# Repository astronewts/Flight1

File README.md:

Flight1
=======

Arduino Code for the 'Around the World' Flight

The flight control software uses a number of custom libraries, to install on a Mac please run:

./installLibraries.sh

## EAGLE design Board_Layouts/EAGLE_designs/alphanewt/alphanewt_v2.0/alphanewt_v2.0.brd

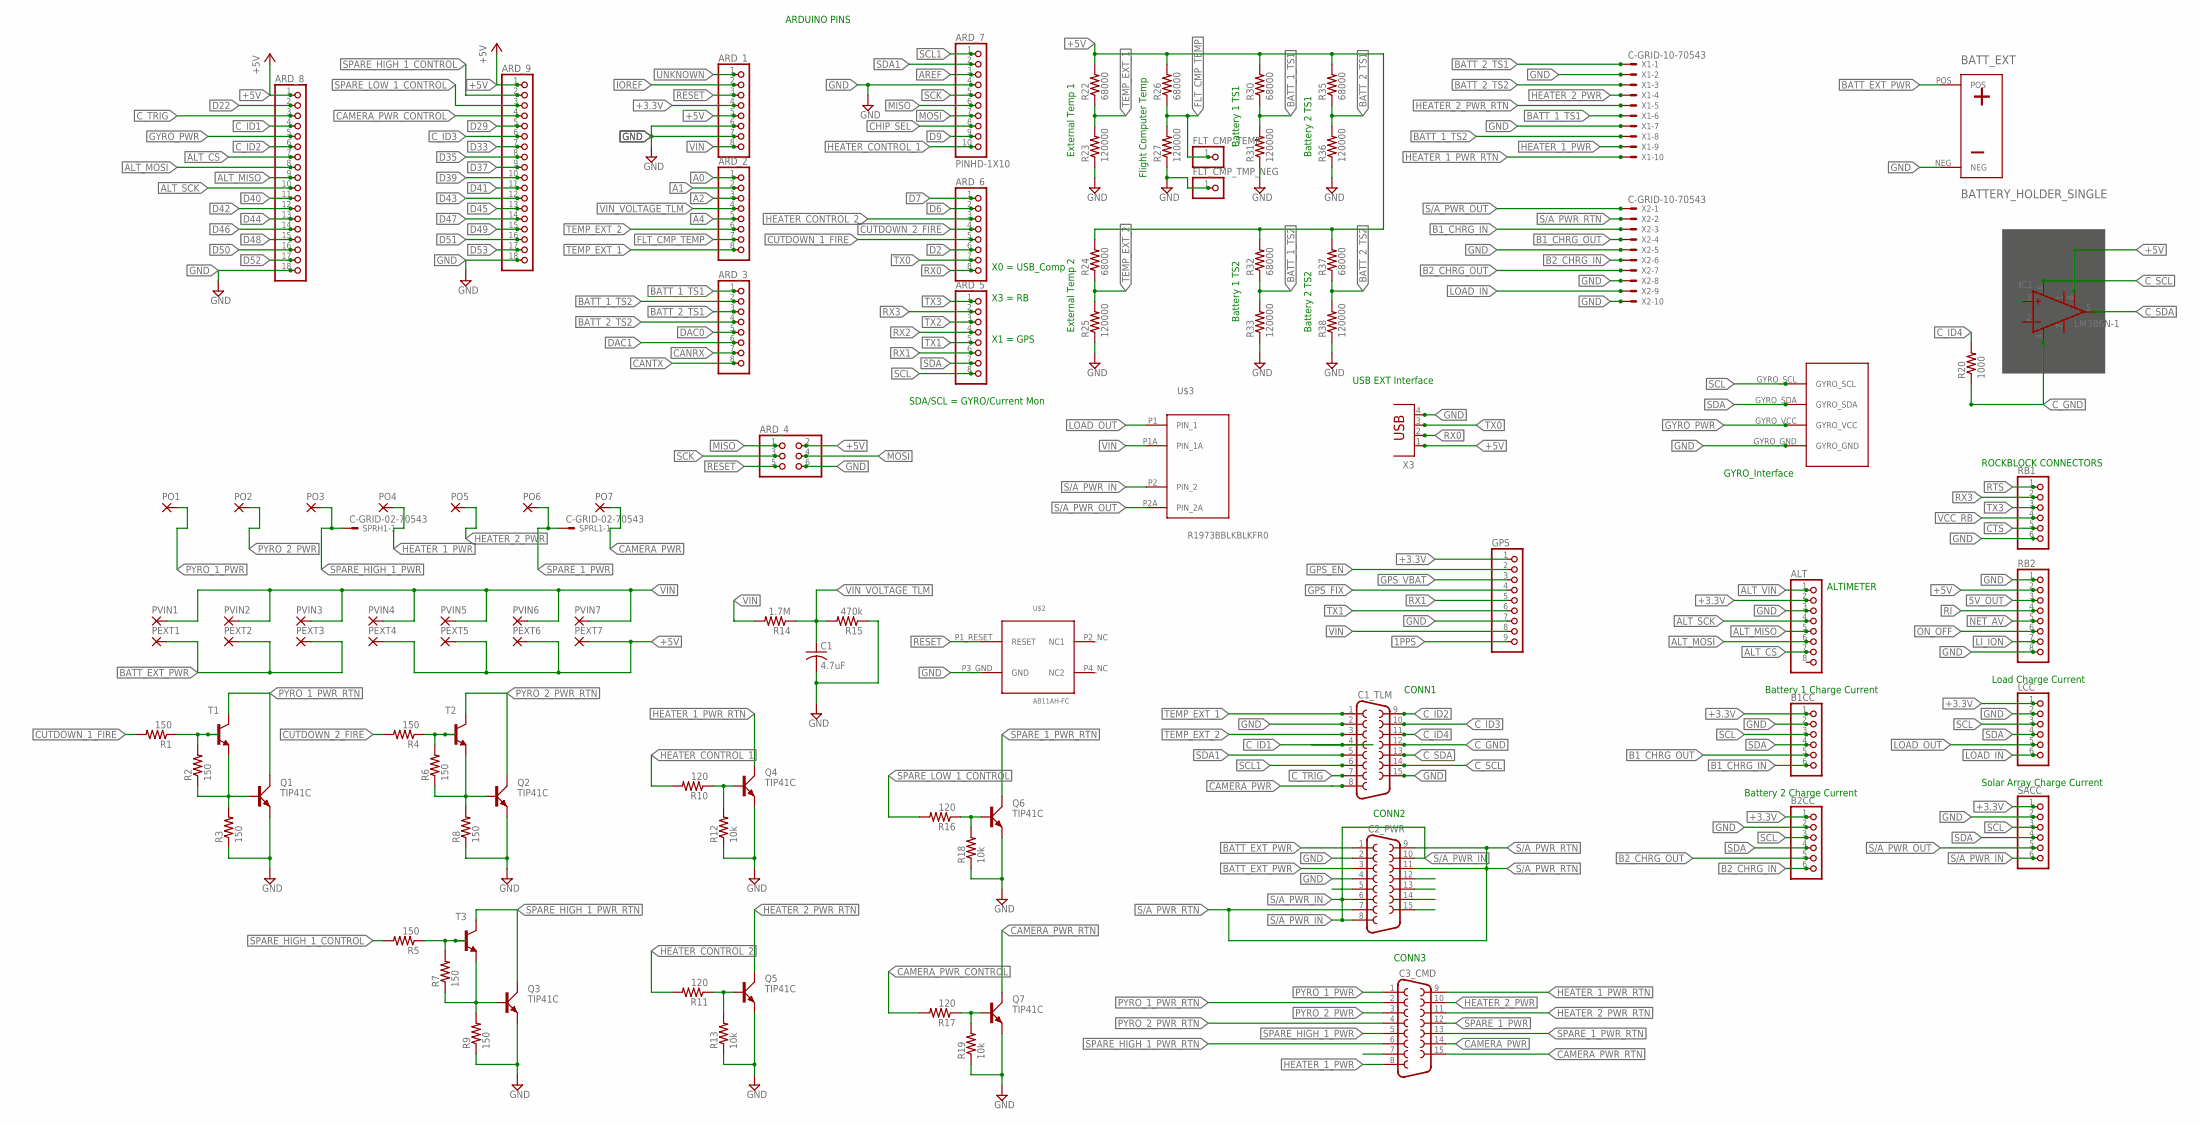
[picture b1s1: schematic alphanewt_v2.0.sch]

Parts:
ALT: PINHD-1X8BIG; 1X08-BIG
ARD_1, ARD_2, ARD_3, ARD_5, ARD_6: PINHD-1X8BIG; 1X08-BIG
ARD_4: PINHD-2X3; 2X03
ARD_7: PINHD-1X10; 1X10-BIG
ARD_8, ARD_9: PINHD-1X18-BIG; 1X18-BIG
B1CC, B2CC: PINHD-1X6B; 1X06-BIG
BATT_EXT: BATTERY_HOLDER_SINGLE; BATT_HOLDER_SINGLE
C1: 4.7uF; C0805K; MPN C2012X6S1H475K125AC
C1_TLM, C2_PWR, C3_CMD: F15HP; MPN 5504F1-15S-02A-03
FLT_CMP_TEMP: PINHD-1X1; 1X01
FLT_CMP_TMP_NEG: PINHD-1X1; 1X01
GPS: PINHD-1X9; 1X09-BIG
IC1: LM386N-1; DIL08
LCC: PINHD-1X6B; 1X06-BIG
PEXT1, PEXT2, PEXT3, PEXT4, PEXT5, PEXT6, PEXT7: SMD2; SMD1,27-2,54
PO1, PO2, PO3, PO4, PO5, PO6, PO7: SMD2; SMD1,27-2,54
PVIN1, PVIN2, PVIN3, PVIN4, PVIN5, PVIN6, PVIN7: SMD2; SMD1,27-2,54
Q1, Q2, Q3, Q4, Q5, Q6, Q7: TIP41C; TO220AV; MPN TIP41C
R1, R2, R3, R4, R5, R6, R7, R8, R9: 150; R0805; MPN CRCW120633R2FKEA
R10, R11, R16, R17: 120; R0805; MPN CRCW120633R2FKEA
R12, R13, R18, R19: 10k; R0805; MPN CRCW120633R2FKEA
R14: 1.7M; R0805; MPN CRCW120633R2FKEA
R15: 470k; R0805; MPN CRCW120633R2FKEA
R20: 1000; R0805; MPN CRCW120633R2FKEA
R22, R24, R26, R30, R32, R35, R37: 68000; R0805; MPN CRCW120633R2FKEA
R23, R25, R27, R31, R33, R36, R38: 120000; R0805; MPN CRCW120633R2FKEA
RB1: PINHD-1X6CB; 1X06-CLEANBIG
RB2: PINHD-1X8BIG; 1X08-BIG
SACC: PINHD-1X6B; 1X06-BIG
SPRH1: C-GRID-02-70543; 70543-02; MPN 70543-0001
SPRL1: C-GRID-02-70543; 70543-02; MPN 70543-0001
T1, T2, T3: 2N3904; TO92; MPN 2N3904
U$2: AB11AH-FC
U$3: R1973BBLKBLKFR0
U$4: GYRO_MPU9250_FOOTPRINT; MPU9250_FOOTPRINT
X1, X2: C-GRID-10-70543; 70543-10
X3: PN87520

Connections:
1PPS: GPS.9
5V_OUT: RB2.3
+3.3V: ALT.2, ARD_1.4, B1CC.1, B2CC.1, GPS.1, LCC.1, SACC.1
+5V: ARD_1.5, ARD_4.2, ARD_8.1, ARD_9.1, IC1.8 (GAIN), PEXT4.1, PEXT5.1, PEXT6.1, PEXT7.1, R22.2, R24.2, R26.2, R30.2, R32.2, R35.2, R37.2, RB2.2, X3.1
A0: ARD_2.1
A1: ARD_2.2
A2: ARD_2.3
A4: ARD_2.5
ALT_CS: ALT.7, ARD_8.7
ALT_MISO: ALT.5, ARD_8.9
ALT_MOSI: ALT.6, ARD_8.8
ALT_SCK: ALT.4, ARD_8.10
ALT_VIN: ALT.1
AREF: ARD_7.3
B1_CHRG_IN: B1CC.6, X2.3
B1_CHRG_OUT: B1CC.5, X2.4
B2_CHRG_IN: B2CC.6, X2.6
B2_CHRG_OUT: B2CC.5, X2.7
BATT_1_TS1: ARD_3.1, R30.1, R31.2, X1.6
BATT_1_TS2: ARD_3.2, R32.1, R33.2, X1.8
BATT_2_TS1: ARD_3.3, R35.1, R36.2, X1.1
BATT_2_TS2: ARD_3.4, R37.1, R38.2, X1.3
BATT_EXT_PWR: BATT_EXT.POS, C2_PWR.1, C2_PWR.3, PEXT1.1, PEXT2.1, PEXT3.1
CAMERA_PWR: C1_TLM.8, C3_CMD.14, PO7.1
CAMERA_PWR_CONTROL: ARD_9.4, R17.2
CAMERA_PWR_RTN: C3_CMD.15, Q7.C
CANRX: ARD_3.7
CANTX: ARD_3.8
CHIP_SEL: ARD_7.8
CTS: RB1.5
CUTDOWN_1_FIRE: ARD_6.5, R1.2
CUTDOWN_2_FIRE: ARD_6.4, R4.2
C_GND: C1_TLM.12, IC1.4 (GND), R20.1
C_ID1: ARD_8.4, C1_TLM.4
C_ID2: ARD_8.6, C1_TLM.9
C_ID3: ARD_9.6, C1_TLM.10
C_ID4: C1_TLM.11, R20.2
C_SCL: C1_TLM.14, IC1.6 (VS)
C_SDA: C1_TLM.13, IC1.5 (OUT)
C_TRIG: ARD_8.3, C1_TLM.7
D2: ARD_6.6
D6: ARD_6.2
D7: ARD_6.1
D9: ARD_7.9
D22: ARD_8.2
D29: ARD_9.5
D33: ARD_9.7
D35: ARD_9.8
D37: ARD_9.9
D39: ARD_9.10
D40: ARD_8.11
D41: ARD_9.11
D42: ARD_8.12
D43: ARD_9.12
D44: ARD_8.13
D45: ARD_9.13
D46: ARD_8.14
D47: ARD_9.14
D48: ARD_8.15
D49: ARD_9.15
D50: ARD_8.16
D51: ARD_9.16
D52: ARD_8.17
D53: ARD_9.17
DAC0: ARD_3.5
DAC1: ARD_3.6
FLT_CMP_TEMP: ARD_2.7, FLT_CMP_TEMP.1, R26.1, R27.2
GND: ALT.3, ARD_1.6, ARD_1.7, ARD_4.6, ARD_7.4, ARD_8.18, ARD_9.18, B1CC.2, B2CC.2, BATT_EXT.NEG, C1.2, C1_TLM.2, C1_TLM.15, C2_PWR.2, C2_PWR.4, FLT_CMP_TMP_NEG.1, GPS.7, LCC.2, Q1.E, Q2.E, Q3.E, Q4.E, Q5.E, Q6.E, Q7.E, R3.1, R8.1, R9.1, R12.1, R13.1, R15.1, R18.1, R19.1, R23.1, R25.1, R27.1, R31.1, R33.1, R36.1, R38.1, RB1.6, RB2.1, RB2.8, SACC.2, U$2.P3_GND (GND), U$4.GYRO_GND, X1.2, X1.7, X2.5, X2.8, X2.10, X3.4
GPS_EN: GPS.2
GPS_FIX: GPS.4
GPS_VBAT: GPS.3
GYRO_PWR: ARD_8.5, U$4.GYRO_VCC
HEATER_1_PWR: C3_CMD.8, PO4.1, X1.9
HEATER_1_PWR_RTN: C3_CMD.9, Q4.C, X1.10
HEATER_2_PWR: C3_CMD.10, PO5.1, X1.4
HEATER_2_PWR_RTN: C3_CMD.11, Q5.C, X1.5
HEATER_CONTROL_1: ARD_7.10, R10.2
HEATER_CONTROL_2: ARD_6.3, R11.2
IOREF: ARD_1.2
LI_ION: RB2.7
LOAD_IN: LCC.6, X2.9
LOAD_OUT: LCC.5, U$3.P1 (PIN_1)
MISO: ARD_4.1, ARD_7.6
MOSI: ARD_4.4, ARD_7.7
unnamed: R4.1, R6.2, T2.2 (B)
unnamed: R1.1, R2.2, T1.2 (B)
unnamed: Q4.B, R10.1, R12.2
unnamed: Q2.B, R6.1, R8.2, T2.3 (E)
unnamed: Q5.B, R11.1, R13.2
unnamed: Q1.B, R2.1, R3.2, T1.3 (E)
unnamed: Q6.B, R16.1, R18.2
unnamed: R5.1, R7.2, T3.2 (B)
unnamed: Q3.B, R7.1, R9.2, T3.3 (E)
unnamed: Q7.B, R17.1, R19.2
NET_AV: RB2.5
ON_OFF: RB2.6
PYRO_1_PWR: C3_CMD.1, PO1.1
PYRO_1_PWR_RTN: C3_CMD.2, Q1.C, T1.1 (C)
PYRO_2_PWR: C3_CMD.3, PO2.1
PYRO_2_PWR_RTN: C3_CMD.4, Q2.C, T2.1 (C)
RESET: ARD_1.3, ARD_4.5, U$2.P1_RESET (RESET)
RI: RB2.4
RTS: RB1.1
RX0: ARD_6.8, X3.2
RX1: ARD_5.6, GPS.5
RX2: ARD_5.4
RX3: ARD_5.2, RB1.2
S/A_PWR_IN: C2_PWR.6, C2_PWR.8, C2_PWR.10, SACC.6, U$3.P2 (PIN_2)
S/A_PWR_OUT: SACC.5, U$3.P2A (PIN_2A), X2.1
S/A_PWR_RTN: C2_PWR.7, C2_PWR.9, C2_PWR.11, X2.2
SCK: ARD_4.3, ARD_7.5
SCL: ARD_5.8, B1CC.3, B2CC.3, LCC.3, SACC.3, U$4.GYRO_SCL
SCL1: ARD_7.1, C1_TLM.6
SDA: ARD_5.7, B1CC.4, B2CC.4, LCC.4, SACC.4, U$4.GYRO_SDA
SDA1: ARD_7.2, C1_TLM.5
SPARE_1_PWR: C3_CMD.12, PO6.1, SPRL1.1
SPARE_1_PWR_RTN: C3_CMD.13, Q6.C
SPARE_HIGH_1_CONTROL: ARD_9.2, R5.2
SPARE_HIGH_1_PWR: C3_CMD.5, PO3.1, SPRH1.1
SPARE_HIGH_1_PWR_RTN: C3_CMD.6, Q3.C, T3.1 (C)
SPARE_LOW_1_CONTROL: ARD_9.3, R16.2
TEMP_EXT_1: ARD_2.8, C1_TLM.1, R22.1, R23.2
TEMP_EXT_2: ARD_2.6, C1_TLM.3, R24.1, R25.2
TX0: ARD_6.7, X3.3
TX1: ARD_5.5, GPS.6
TX2: ARD_5.3
TX3: ARD_5.1, RB1.3
UNKNOWN: ARD_1.1
VCC_RB: RB1.4
VIN: ARD_1.8, GPS.8, PVIN1.1, PVIN2.1, PVIN3.1, PVIN4.1, PVIN5.1, PVIN6.1, PVIN7.1, R14.2, U$3.P1A (PIN_1A)
VIN_VOLTAGE_TLM: ARD_2.4, C1.1, R14.1, R15.2

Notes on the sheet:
External Temp 1
External Temp 2
Flight Computer Temp
Battery 1 TS1
Battery 1 TS2
Battery 2 TS1
Battery 2 TS2
GYRO_Interface
ALTIMETER
Battery 1 Charge Current
Battery 2 Charge Current
Solar Array Charge Current
Load Charge Current
ROCKBLOCK CONNECTORS
ARDUINO PINS
CONN1
CONN2
CONN3
USB EXT Interface
X3 = RB
SDA/SCL = GYRO/Current Mon
X0 = USB_Comp
X1 = GPS

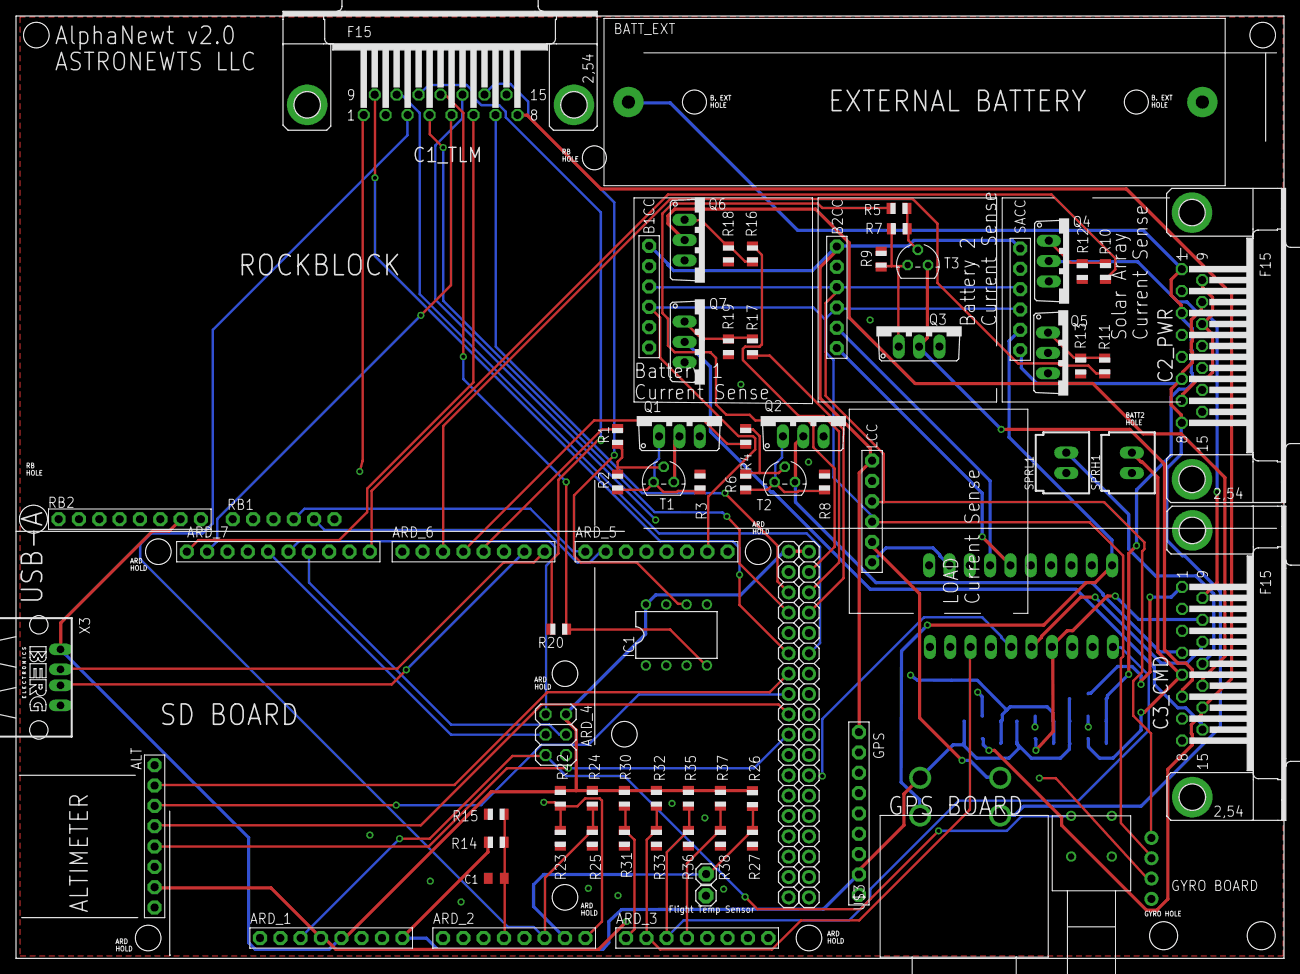
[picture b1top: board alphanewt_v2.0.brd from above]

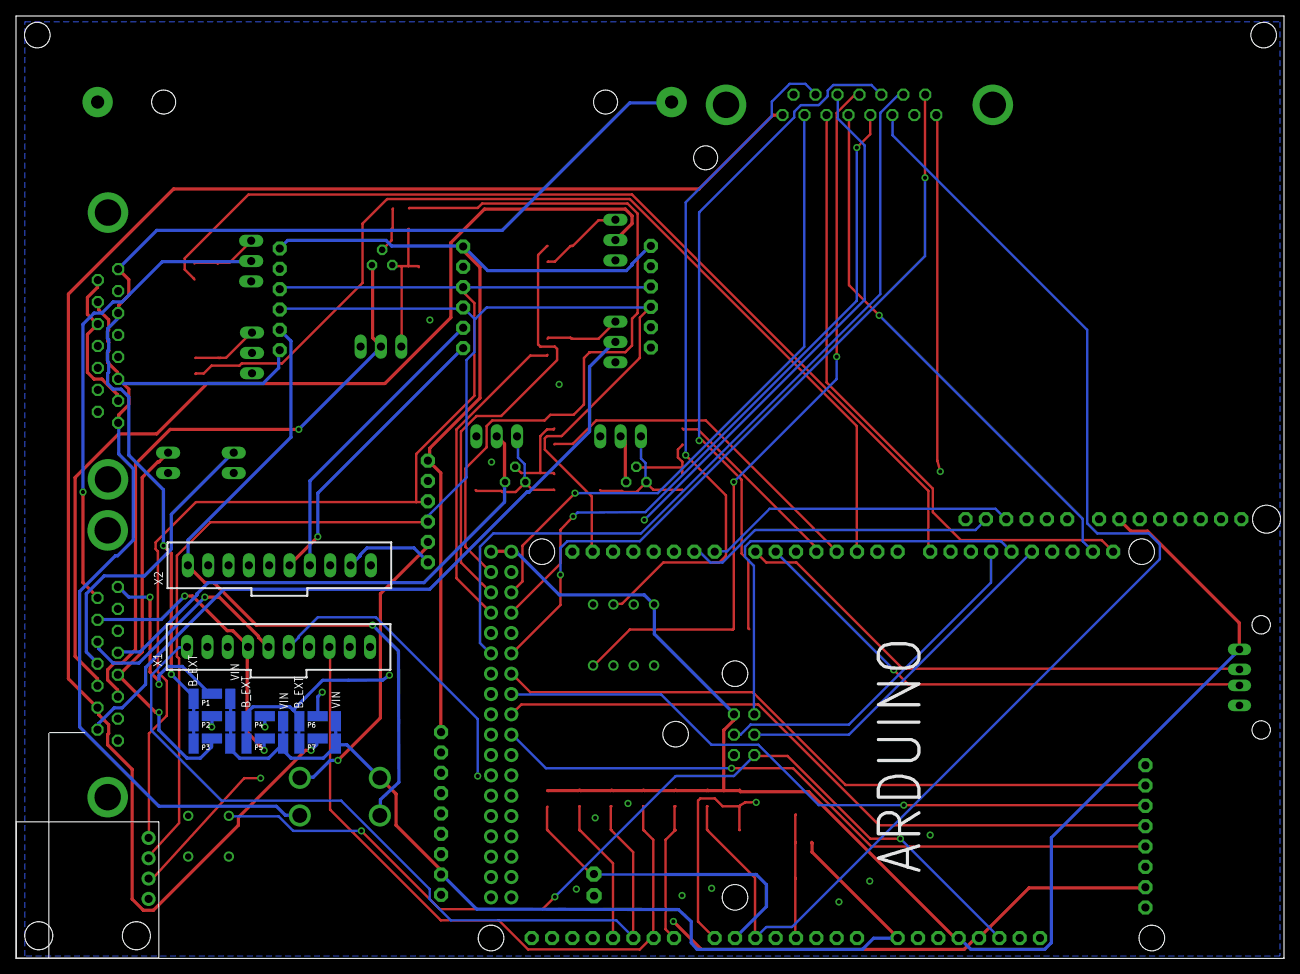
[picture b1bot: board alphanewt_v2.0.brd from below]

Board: 4 copper layers, 158.4 x 117.7 mm, 98 parts (24 on the bottom side), 80 nets.

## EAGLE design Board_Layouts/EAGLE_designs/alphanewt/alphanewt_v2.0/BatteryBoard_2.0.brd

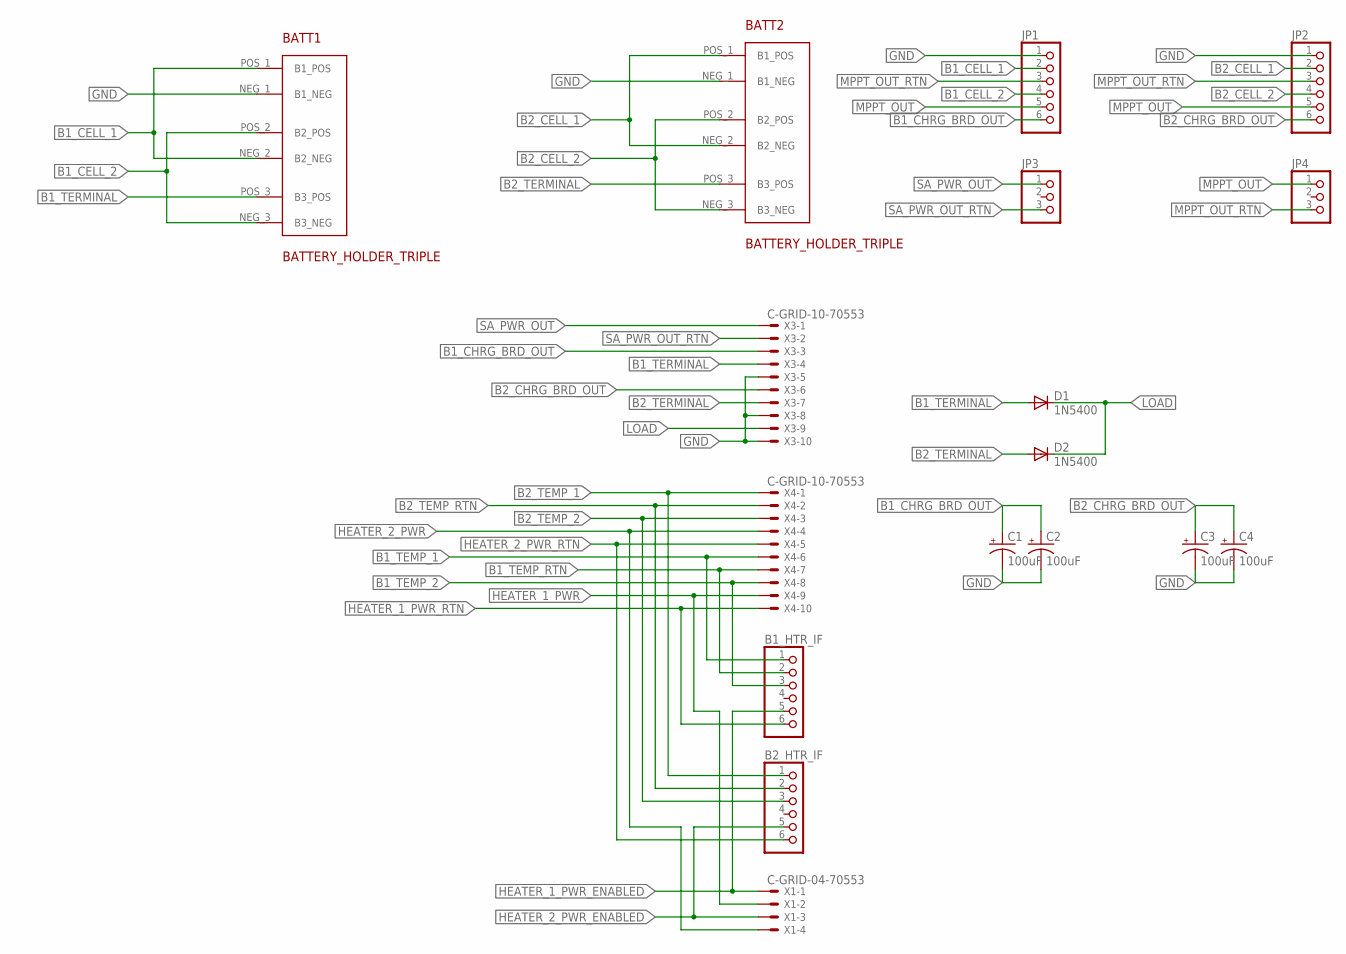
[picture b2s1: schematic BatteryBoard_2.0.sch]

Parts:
B1_HTR_IF, B2_HTR_IF: PINHD-1X6CLEAN; 1X06-CLEAN
BATT1, BATT2: BATTERY_HOLDER_TRIPLE; BATT_HOLDER_SINGLE
C1, C2, C3, C4: 100uF; CT7343
D1, D2: 1N5400; DO201-15
JP1, JP2: PINHD-1X6CLEAN; 1X06-CLEAN
JP3, JP4: PINHD-1X3; 1X03
X1: C-GRID-04-70553; 70553-04
X3, X4: C-GRID-10-70553; 70553-10

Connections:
B1_CELL_1: BATT1.NEG_2 (B2_NEG), BATT1.POS_1 (B1_POS), JP1.2
B1_CELL_2: BATT1.NEG_3 (B3_NEG), BATT1.POS_2 (B2_POS), JP1.4
B1_CHRG_BRD_OUT: C1.+, C2.+, JP1.6, X3.3
B1_TEMP_1: B1_HTR_IF.1, X4.6
B1_TEMP_2: B1_HTR_IF.3, X4.8
B1_TEMP_RTN: B1_HTR_IF.2, X4.7
B1_TERMINAL: BATT1.POS_3 (B3_POS), D1.A, X3.4
B2_CELL_1: BATT2.NEG_2 (B2_NEG), BATT2.POS_1 (B1_POS), JP2.2
B2_CELL_2: BATT2.NEG_3 (B3_NEG), BATT2.POS_2 (B2_POS), JP2.4
B2_CHRG_BRD_OUT: C3.+, C4.+, JP2.6, X3.6
B2_TEMP_1: B2_HTR_IF.1, X4.1
B2_TEMP_2: B2_HTR_IF.3, X4.3
B2_TEMP_RTN: B2_HTR_IF.2, X4.2
B2_TERMINAL: BATT2.POS_3 (B3_POS), D2.A, X3.7
GND: BATT1.NEG_1 (B1_NEG), BATT2.NEG_1 (B1_NEG), C1.-, C2.-, C3.-, C4.-, JP1.1, JP2.1, X3.5, X3.8, X3.10
HEATER_1_PWR: X1.2, X4.9
HEATER_1_PWR_ENABLED: B1_HTR_IF.5, X1.1
HEATER_1_PWR_RTN: B1_HTR_IF.6, X4.10
HEATER_2_PWR: X1.4, X4.4
HEATER_2_PWR_ENABLED: B2_HTR_IF.5, X1.3
HEATER_2_PWR_RTN: B2_HTR_IF.6, X4.5
LOAD: D1.C, D2.C, X3.9
MPPT_OUT: JP1.5, JP2.5, JP4.1
MPPT_OUT_RTN: JP1.3, JP2.3, JP4.3
SA_PWR_OUT: JP3.1, X3.1
SA_PWR_OUT_RTN: JP3.3, X3.2

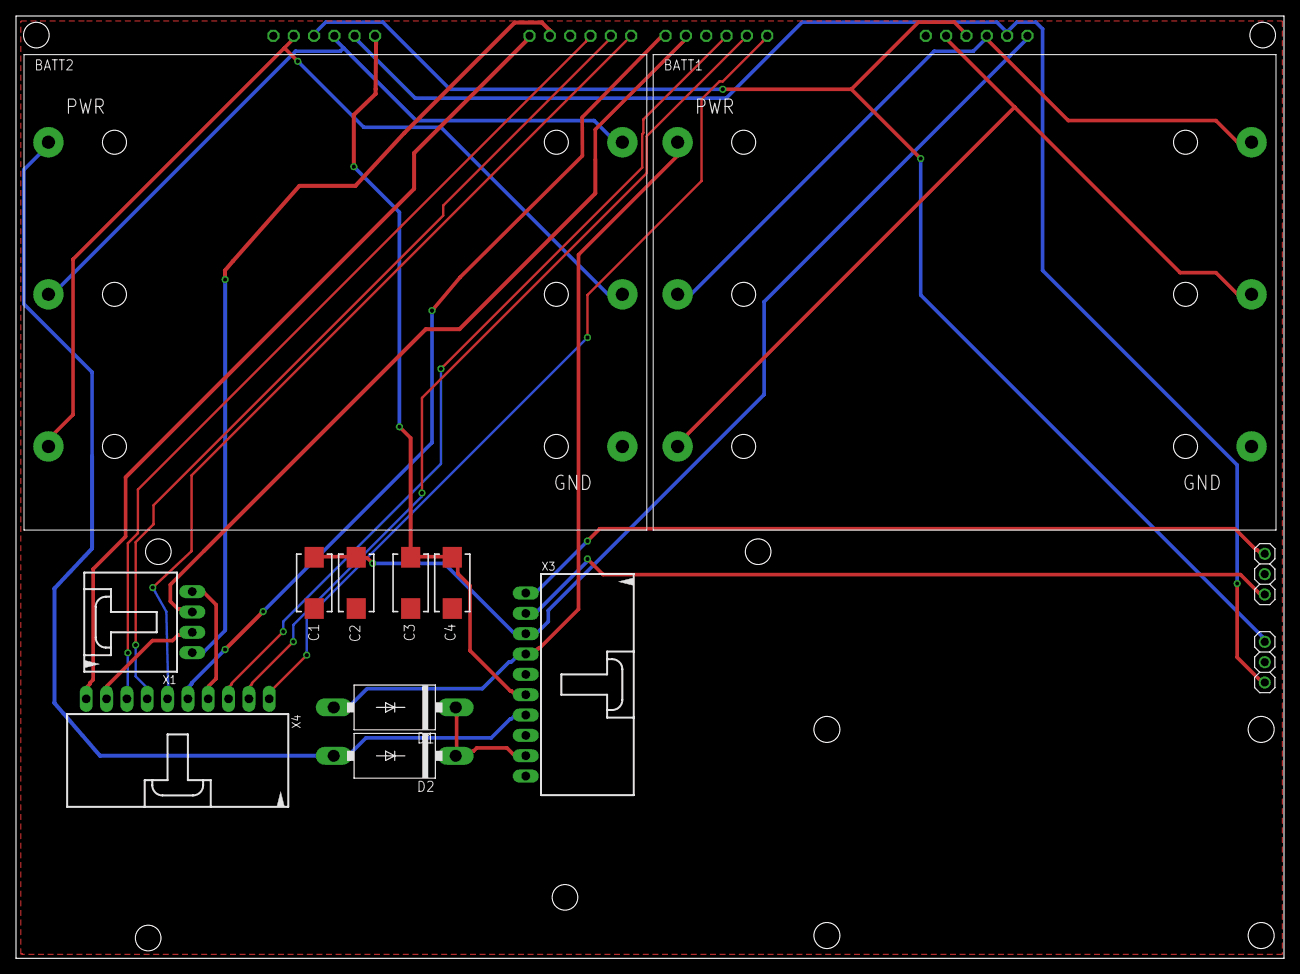
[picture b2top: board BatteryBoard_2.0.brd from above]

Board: 2 copper layers, 158.4 x 117.7 mm, 17 parts (0 on the bottom side), 26 nets.

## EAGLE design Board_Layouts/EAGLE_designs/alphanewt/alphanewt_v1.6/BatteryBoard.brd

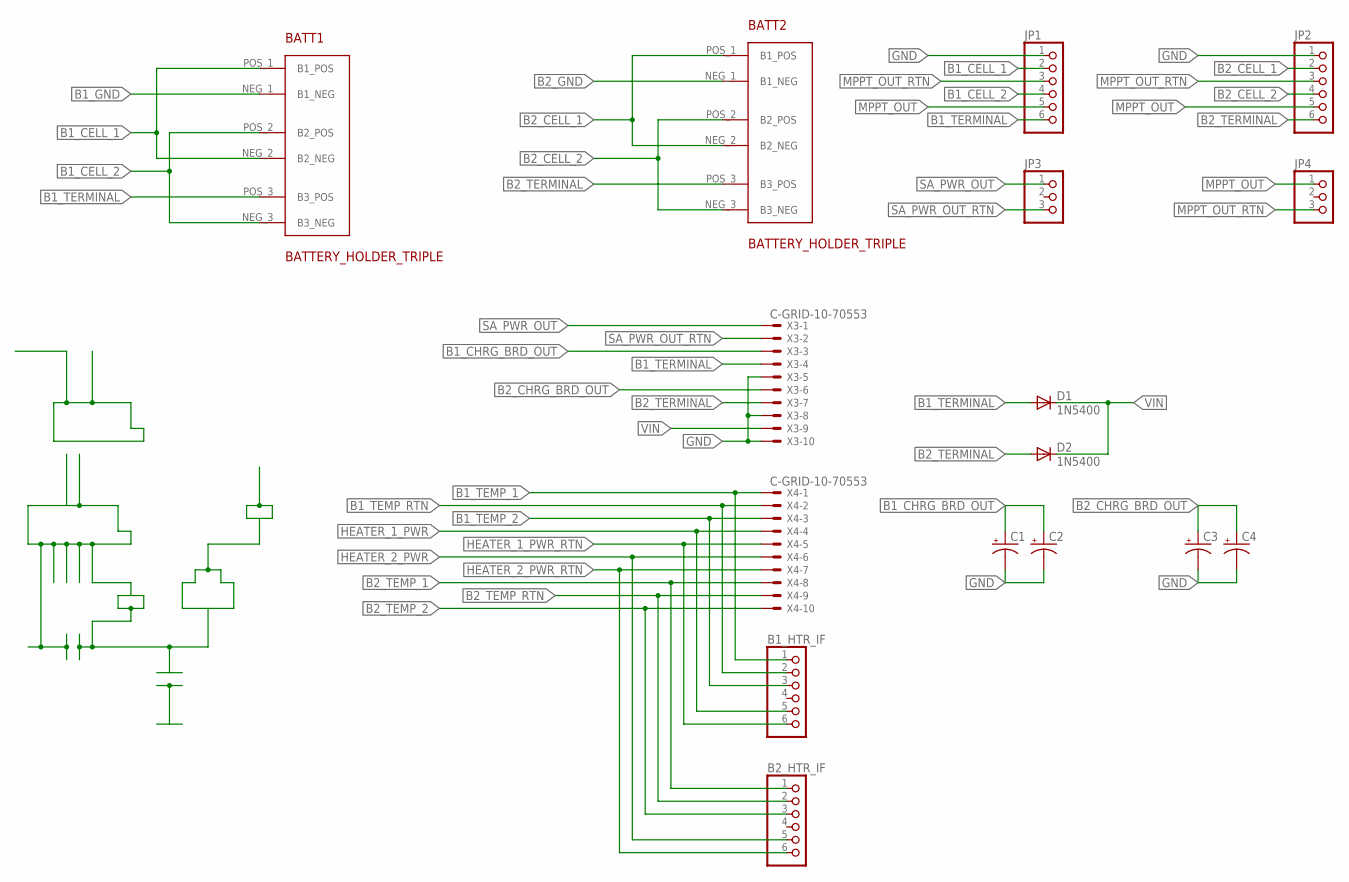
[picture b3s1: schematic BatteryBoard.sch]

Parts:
B1_HTR_IF, B2_HTR_IF: PINHD-1X6CLEAN; 1X06-CLEAN
BATT1, BATT2: BATTERY_HOLDER_TRIPLE; BATT_HOLDER_SINGLE
C1, C2, C3, C4: CPOL-USCT7343; CT7343
D1, D2: 1N5400; DO201-15
JP1, JP2: PINHD-1X6CLEAN; 1X06-CLEAN
JP3, JP4: PINHD-1X3; 1X03
X3, X4: C-GRID-10-70553; 70553-10

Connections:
B1_CELL_1: BATT1.NEG_2 (B2_NEG), BATT1.POS_1 (B1_POS), JP1.2
B1_CELL_2: BATT1.NEG_3 (B3_NEG), BATT1.POS_2 (B2_POS), JP1.4
B1_CHRG_BRD_OUT: C1.+, C2.+, X3.3
B1_GND: BATT1.NEG_1 (B1_NEG)
B1_TEMP_1: B1_HTR_IF.1, X4.1
B1_TEMP_2: B1_HTR_IF.3, X4.3
B1_TEMP_RTN: B1_HTR_IF.2, X4.2
B1_TERMINAL: BATT1.POS_3 (B3_POS), D1.A, JP1.6, X3.4
B2_CELL_1: BATT2.NEG_2 (B2_NEG), BATT2.POS_1 (B1_POS), JP2.2
B2_CELL_2: BATT2.NEG_3 (B3_NEG), BATT2.POS_2 (B2_POS), JP2.4
B2_CHRG_BRD_OUT: C3.+, C4.+, X3.6
B2_GND: BATT2.NEG_1 (B1_NEG)
B2_TEMP_1: B2_HTR_IF.1, X4.8
B2_TEMP_2: B2_HTR_IF.3, X4.10
B2_TEMP_RTN: B2_HTR_IF.2, X4.9
B2_TERMINAL: BATT2.POS_3 (B3_POS), D2.A, JP2.6, X3.7
GND: C1.-, C2.-, C3.-, C4.-, JP1.1, JP2.1, X3.5, X3.8, X3.10
HEATER_1_PWR: B1_HTR_IF.5, X4.4
HEATER_1_PWR_RTN: B1_HTR_IF.6, X4.5
HEATER_2_PWR: B2_HTR_IF.5, X4.6
HEATER_2_PWR_RTN: B2_HTR_IF.6, X4.7
MPPT_OUT: JP1.5, JP2.5, JP4.1
MPPT_OUT_RTN: JP1.3, JP2.3, JP4.3
SA_PWR_OUT: JP3.1, X3.1
SA_PWR_OUT_RTN: JP3.3, X3.2
VIN: D1.C, D2.C, X3.9

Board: 2 copper layers, 16 parts (0 on the bottom side), 24 nets, no tracks yet.

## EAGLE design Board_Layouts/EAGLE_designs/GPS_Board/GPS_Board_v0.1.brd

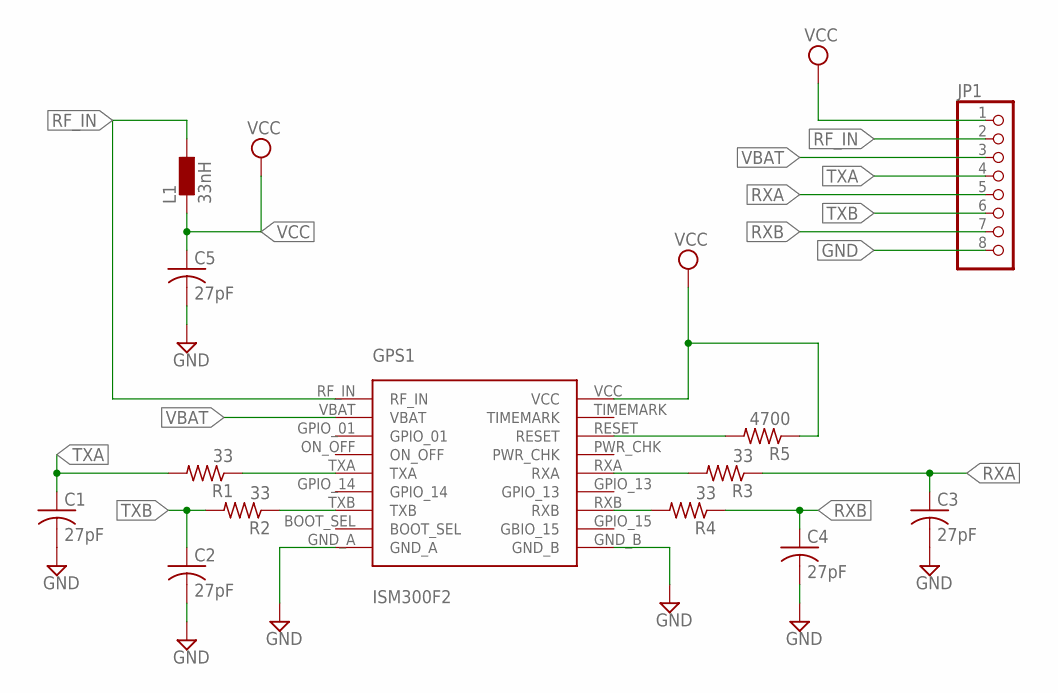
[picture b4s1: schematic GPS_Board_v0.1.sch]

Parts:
C1, C2, C3, C4, C5: 27pF; C0805K; MPN C0805C270J5GACTU
GPS1: ISM300F2
JP1: PINHD-1X8BIG; 1X08-BIG
L1: 33nH; L4532P; MPN MCWL06KT33N
R1, R2, R3, R4: 33; R0805; MPN CRCW120633R2FKEA
R5: 4700; R0805; MPN CRCW12104K70FKEA

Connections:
GND: C1.2, C2.2, C3.2, C4.2, C5.2, GPS1.GND_A, GPS1.GND_B, JP1.8
unnamed: GPS1.RESET, R5.2
unnamed: GPS1.TXB, R2.1
unnamed: GPS1.TXA, R1.1
unnamed: GPS1.RXB, R4.2
unnamed: GPS1.RXA, R3.2
RF_IN: GPS1.RF_IN, JP1.2, L1.1
RXA: C3.1, JP1.5, R3.1
RXB: C4.1, JP1.7, R4.1
TXA: C1.1, JP1.4, R1.2
TXB: C2.1, JP1.6, R2.2
VBAT: GPS1.VBAT, JP1.3
VCC: C5.1, GPS1.VCC, JP1.1, L1.2, R5.1

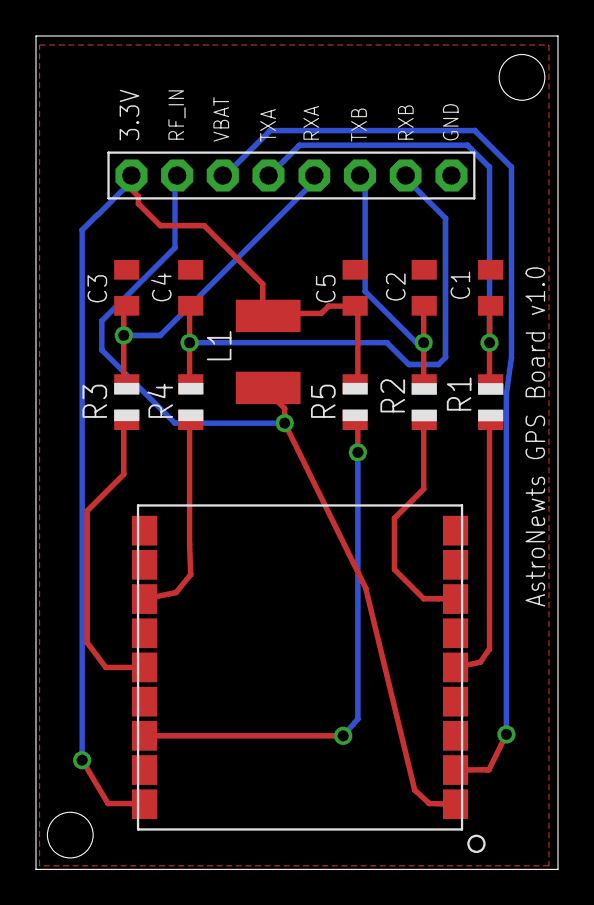
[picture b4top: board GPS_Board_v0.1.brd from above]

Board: 2 copper layers, 29.0 x 46.3 mm, 13 parts (0 on the bottom side), 13 nets.

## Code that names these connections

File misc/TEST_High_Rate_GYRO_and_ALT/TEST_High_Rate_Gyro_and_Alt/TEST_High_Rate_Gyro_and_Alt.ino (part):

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  digitalWrite(PIN_BATTERY_1_CHARGE_CUTOFF, LOW);
  digitalWrite(PIN_BATTERY_2_CHARGE_CUTOFF, LOW);
  digitalWrite(PIN_CUTDOWN_ENABLE, LOW);
  digitalWrite(PIN_CUTDOWN_1_FIRE, LOW);
  digitalWrite(PIN_CUTDOWN_2_FIRE, LOW);
  
  digitalWrite(PIN_HEATER_CONTROL_1, LOW);
  digitalWrite(PIN_HEATER_CONTROL_2, LOW);
  
  // Change the analog read resolution to 12 bits
  analogReadResolution(RESOLUTION_PRESSURE_SENSOR);
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   pinMode(SD_CHIP_SELECT, OUTPUT);
   pinMode(PIN_BATTERY_1_CHARGE_CUTOFF, OUTPUT);
   pinMode(PIN_BATTERY_2_CHARGE_CUTOFF, OUTPUT);
   pinMode(PIN_HEATER_CONTROL_1, OUTPUT);
   pinMode(PIN_HEATER_CONTROL_2, OUTPUT);
   pinMode(PIN_CUTDOWN_ENABLE, OUTPUT);
   pinMode(PIN_CUTDOWN_1_FIRE, OUTPUT);
   pinMode(PIN_CUTDOWN_2_FIRE, OUTPUT);
   pinMode(PIN_CAMERA_SWITCH, OUTPUT);
   
   
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   parameters.cutdown_enable_state = true;
   
   //Set primary pin to high
   digitalWrite(PIN_CUTDOWN_1_FIRE, HIGH);
   parameters.cutdown_1_status = true;
   
   //Mark time that pyro was initiated 
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
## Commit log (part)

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2015-06-07 Refactor gyro module
2015-06-07 Fix double add of vehicle mode
2015-06-07 Remove stale comment
2015-06-07 Rename sd_card_write_rate to period, fix command conversions
2015-06-07 matlab routine to convert rockblock data into understandable stuffs.
2015-06-07 some cleaning ...
2015-06-08 better version of the converter
2015-06-08 fix a few bugs in the matlab decoder
2015-06-08 changed all analog Tlm output as Counts in the rockblock module, & changed charge current from 32float to 12bit count
2015-06-08 some cleaning
2015-06-08 Rename function
2015-06-08 Fix return types
2015-06-08 Fix return types?
2015-06-08 Switch back to uint32_t for read
2015-06-08 fix bug
2015-06-08 Updated Matlab decoder output format and added units
2015-06-08 Re-added the collect_telemetry() function into the beging of the flight processing loop
2015-06-09 Update Matlab output indexvalues to start at 0
2015-06-09 more comments in the post-processing matlab
2015-06-09 new stuffs
2015-06-09 looks like I missed a few delays ... sigh
2015-06-09 Fixed SD card write error crash issue
2015-06-09 Added all the hooks for the altimiter data to the RB mod and both the SD and TLM modules
2015-06-10 whoops ... missed a bracket ...
2015-06-10 new comments
2015-06-11 Document altitude unit
2015-06-11 Re-add row-telemetry print out
2015-06-13 Transmit temperature conversion constants in telemetry
2015-06-13 Fix a few syntax errors
2015-06-17 Updated Matlab ground code to output temperatures in deg C
2015-06-17 changed the base path to look at the directory where the matlab is being run in, and creates a data folder
2015-06-17 Fixed serial print of heater setpoint threshold notification
2015-06-23 Comment most processes for RockBlock signal quality debugging
2015-07-03 add web address of rockblock interface to flight code.
2015-07-08 correct wrong string in ground decoder.
2015-07-08 Switch to three digit logging, log float with more precision
2015-07-08 correction of the transmission of the Tre from the gyro
2015-07-10 new version of emergency cutdown based on altitude
2015-07-10 oops forgot to uncomment call sendreceive_satellite_data() in flight
2015-07-11 add a counter to the emergency cutdown based on alt. this is to avoid triggering in case of an error.
2015-09-17 serial output to work on cleaning code
2015-10-14 Updated RB test loop to verify the order and timing of various actions
2015-11-05 Tweaks & updates for part one of 11/4/15 jam session on code overhaul
2015-11-05 removed the terminal output for the Battery Temp Avg TLM as being written out to buffer
2015-11-07 corrected commented out bracket error in previous lib update
2015-11-07 modify test of the initial prompt by user to make everything super clear.
2015-11-18 OOps I did it again
2015-11-22 Revert "Updated the code base to account for high speed and slow speed looping"
    This reverts commit 043fed6a416827fa0ce6c8edf722289919af53d5.
2015-11-25 Cleaned up RB Code Base a bit more - fixed comments, terminal out
2015-12-08 Remove all display-related code
2015-12-08 some more comments during initialization step
2015-12-15 Fixed casting error in the calculate_temp function
2015-12-15 Fixed Temp Sensor error in the calculate_temp() function - It works correctly now
2015-12-15 add final comment for initialization
    modified: bin/Flight/rockblock_module.ino
2015-12-15 commented sd_init, rb_init and gyro_init
2016-01-07 Add error checking to byte-write and attempt to deactivate sleep
2016-01-07 Add error checking to sensor read
2016-01-12 refine scaling value in baro lib to get correct altitude
2016-01-12 Some test only lines added in to the Terminal Test
2016-01-12 Fuck you gyro
2016-01-12 Write gyro to SD
2016-01-20 update of the RB code
2016-01-20 Remove serial speed redefinition, reorder startup
2016-01-20 cleaning up trash that nick left. Also, removed RB_Debug mode
2016-01-20 Finite gyro setup retry instead of infinite
2016-01-20 Updated camera module to fix a potential error with camera on time reset
2016-01-28 Add header to the SD card write
2016-01-30 Shorten names in SD card
2016-01-30 Change gyro power pin for flight
2016-01-30 remove the Fail While in gyro setup
2016-01-30 Fix minor things in header and units in SD card
2016-01-31 Newlines, not /n
2016-02-26 Moved the Gyro initialization Pin to the definitions and the nominal output pin setup, and updated the correct pin number.
2016-02-26 Minor fix in the gyro_setup that made the code crash
2016-02-26 Minor reorg of telemetry processing tasks
2016-02-26 Hacky removal of spammy I2C debug logs
2016-03-03 Change Cutdown test for have high rate before cutdown
2016-03-15 Fix misnamed pin
2016-03-15 Some new goodies for Sig Quality test.
2016-03-15 last cleanup of Signal Quality test mode.
2016-03-25 Write hex code
2016-03-25 Consistency
2016-03-25 Remove useless code
2016-04-07 clearer comments
2016-04-07 After checkout with double loop RAw and HEX
2016-04-14 UPDATED IRIDIUMSBD LIB FINALLY WORKS. Race condition internal to the RB finally works
2016-04-16 Update post-process script
2016-04-16 DISABLE Heaters On/OFF evaluation until we proof out the temp problems
2016-05-03 Guard against multiple includes
2016-05-10 Small update of the csv post-process script
2016-05-17 With callback function in the RB - WORKS - LOG082
2016-05-18 MAJOR CHANGES IN FLIGHT LOOP DESIGN, ADD RB FLAG TO SD, ADD NEW MODES...
2016-05-22 Added the new current sensors to the code base, added hooks into the sub modules, & folder cleanup
2016-05-22 Added EAGLE drawings to jam out on
2016-06-11 Added Solar Array Current sensors and Load Current Sensors. Tested & they work (WOOHOO)
2016-06-17 Enforce consistent spacing in gyro_module.ino
2016-06-17 Enforce consistent spacing in sd_module.ino
2016-06-17 Add debug_println macro
2016-06-20 Additional bit-packed items (work in progress)
2016-06-21 Add lat/long conversion functions
2016-06-21 Give TinyGPS 10 milliseconds to do its processing (instead of 0)
2016-06-21 Stop breaking the build
2016-06-21 Just add a triangular filter if you want to filter data
2016-06-21 Try to update with Board_layouts
2016-06-28 Add SD_write in telemetry and go back to old SD file
2016-06-28 Giving up on SD name (for now)
2016-06-28 Avoid confusion
2016-07-07 modify the weird conditional at the end of the module that was causing the "DONE" issue + the closing of the SD file.
2016-07-14 Just changes in the post-process script
2016-07-18 Remove post-process script from FLight code
2016-07-20 code clean up post high rate battery charging test
2016-07-20 moved the added RB struct's to the top of the global list in the Flight section
2016-08-03 updated code to limit the file size and then create a new sequential one
2016-08-04 corrected Core7 URL, and uncommented altimeter data collection in Terminal Test
2016-08-28 Massive overhaul on the code base. RB and SD output words now source the same place. Compiles, but needs lots of testing
2016-08-28 couple of code bug corrections. work around for current sense #3 address issue (?)
2016-08-28 Removed all the pointer references to make it easier. Refer back to previous push to contine using pointers
2016-08-28 fixed the RB word output header
2016-08-30 minor updates
2016-09-08 updated Flight DB to include additional Format, and added the Format TLM, and time slot
2016-09-08 Second set of tools to decode RB
2016-09-08 updated all the hooks to update the Flight Format and updated the database
2016-09-08 Added final code hooks for the implement chosing which format
2016-09-09 ensured that the writetoSDcard command was invoked everytime we have a major PL event
2016-09-13 add test to ensure RB mssg is not too long and can be sent.
2016-09-13 revert changes on the initialization of the db
2016-09-13 fix the offbyone errors for cycling through the db
2016-09-13 added post_process calls to the flight and test loops
2016-09-13 corrected charge current vars in DB format 2
2016-09-15 updated the cutdown status to be the cutdown event flag. Other minor improvements
2016-09-15 new database from Arduino
2016-09-15 Update Read database
2016-09-27 use universal time since beginning
2016-09-30 Just change millis to Elapsed time
2016-09-30 New SD card reader using Database_Arduino
2016-09-30 elapsed time [s] => [ms] in 1st SD column
2016-09-30 cleanup on the SD_num in the RB word, other RB debug mode terminal formatting, better labeling, etc
2016-10-07 database update and comment clean-up
2016-10-07 Centralize read RB and SD data
2016-10-07 update database for RB and SD decoder
2016-10-07 fixed DB error in active tran rate
2016-10-11 Correct time/1000 based on analysis of LOG160
2016-10-18 corrected issue with the Battery Voltage/Current flags erroneously tripping
2016-10-22 Code base updates for Round 1 Commanding verification. cleaned up ground to flight unit converion, aligned altitiude to meters.
2016-10-26 synch database
2016-11-05 Convert C to K because Luis did not do it last time
2016-11-05 Post-process update
2016-11-05 Re change temperatures so we don't add 273 to counts
2016-11-06 bug in telemetry module when testing Tre to switch heater fix: remove || operator in evaluate_heater_state permutation of the analog pin to have correct heater and T sensor on each battery
2016-11-08 Clean the SD card reading tool
2016-11-08 Big clean of the post-process code
2016-11-08 Actually last push was a lie
2016-11-08 minor tweaks
2017-01-17 Added Autonomous Test Suite Comments, GPS Module hook to the common data structure, Call-back non-exculsion of modes, corrected incorrect sanity check overwrite, and a slew of small things
2017-01-17 recommiting over Nick's last commit
2017-01-17 minor change (space) to get last commit after merge deal
2017-02-10 fix the potential division by zero in altimeter lib.
2017-02-10 Added BMP280 libraries and test code for new Board #1
2017-02-14 Fix Mode and signal quality mode
2017-02-27 corrected the revert back to an old IN219 library. Current sense now works correctly
2017-02-28 Update Database and automatic data check
2017-03-05 Added logic in the low voltage cutdown to go straight to cutdown if the voltage is too too low, and some walls to not go through the cutdown logic if we have cutdown already. Additional beta board up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
2017-03-07 fixed code bug in last push
2017-03-07 new comments in telem for voltage auto cutdown
2017-03-07 add debug mode to flight without RB
2017-03-07 add debug mode for execute electrical control check
2017-03-07 comment updates to telem module, and mode exclusion for battery voltage cutdown test
2017-03-20 Update database, step2 for figures and period for RB
2017-03-24 added code comments for test
2017-03-28 some update on the post-processing
2017-03-28 Added signal quality output to the SD card for Interference/signal quality test
2017-03-30 definitions update for close-to-real numbers pre-day-in-the-life-test #1
2017-05-03 updated GPS Board layout v1.0 ready for production review
2017-07-05 updated alphanewt layout with FLT Temp, added board labels, and included the Drill file
2017-07-15 Updated the design to no longer use blind vias. v1.3 is the one being built
2017-08-05 new lib for the gyro
2017-09-18 Uploading alphanewt 1.5, and a Camera mod change
2017-11-14 Adding updated v1.7 alphanewt boards. Not routed yet
2017-11-18 Major update to alphanewt 1.8. Almost done routing the logic board.
2017-12-07 updated GPS baud rate to 9600 accomodate Ultimate GPS
2017-12-10 Update the MATLAB post-processing code
2017-12-10 moved GSP collectfrom the high freq to the medium freq section
2017-12-10 move more tlm to the MEDIUM rate section in Flight
2017-12-10 New MATLAB post-processing
2017-12-10 Start to clean the data
2017-12-11 Update MATLAB tools
2017-12-11 Remove a MATLAB asv file
2017-12-17 added hooks to put the GPS module to sleep every once in a while
2017-12-26 Added code base used to successfully program the EEPROM, in addition to a handful of Gyro tests
2018-01-29 Minor change to post-processing script
2018-04-15 Flight Code updates from 72 hr testing, and some camera script progress

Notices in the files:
misc/TEST_High_Rate_GYRO_and_ALT/TEST_High_Rate_Gyro_and_Alt/TEST_High_Rate_Gyro_and_Alt.ino:
Open Source / Public Domain
